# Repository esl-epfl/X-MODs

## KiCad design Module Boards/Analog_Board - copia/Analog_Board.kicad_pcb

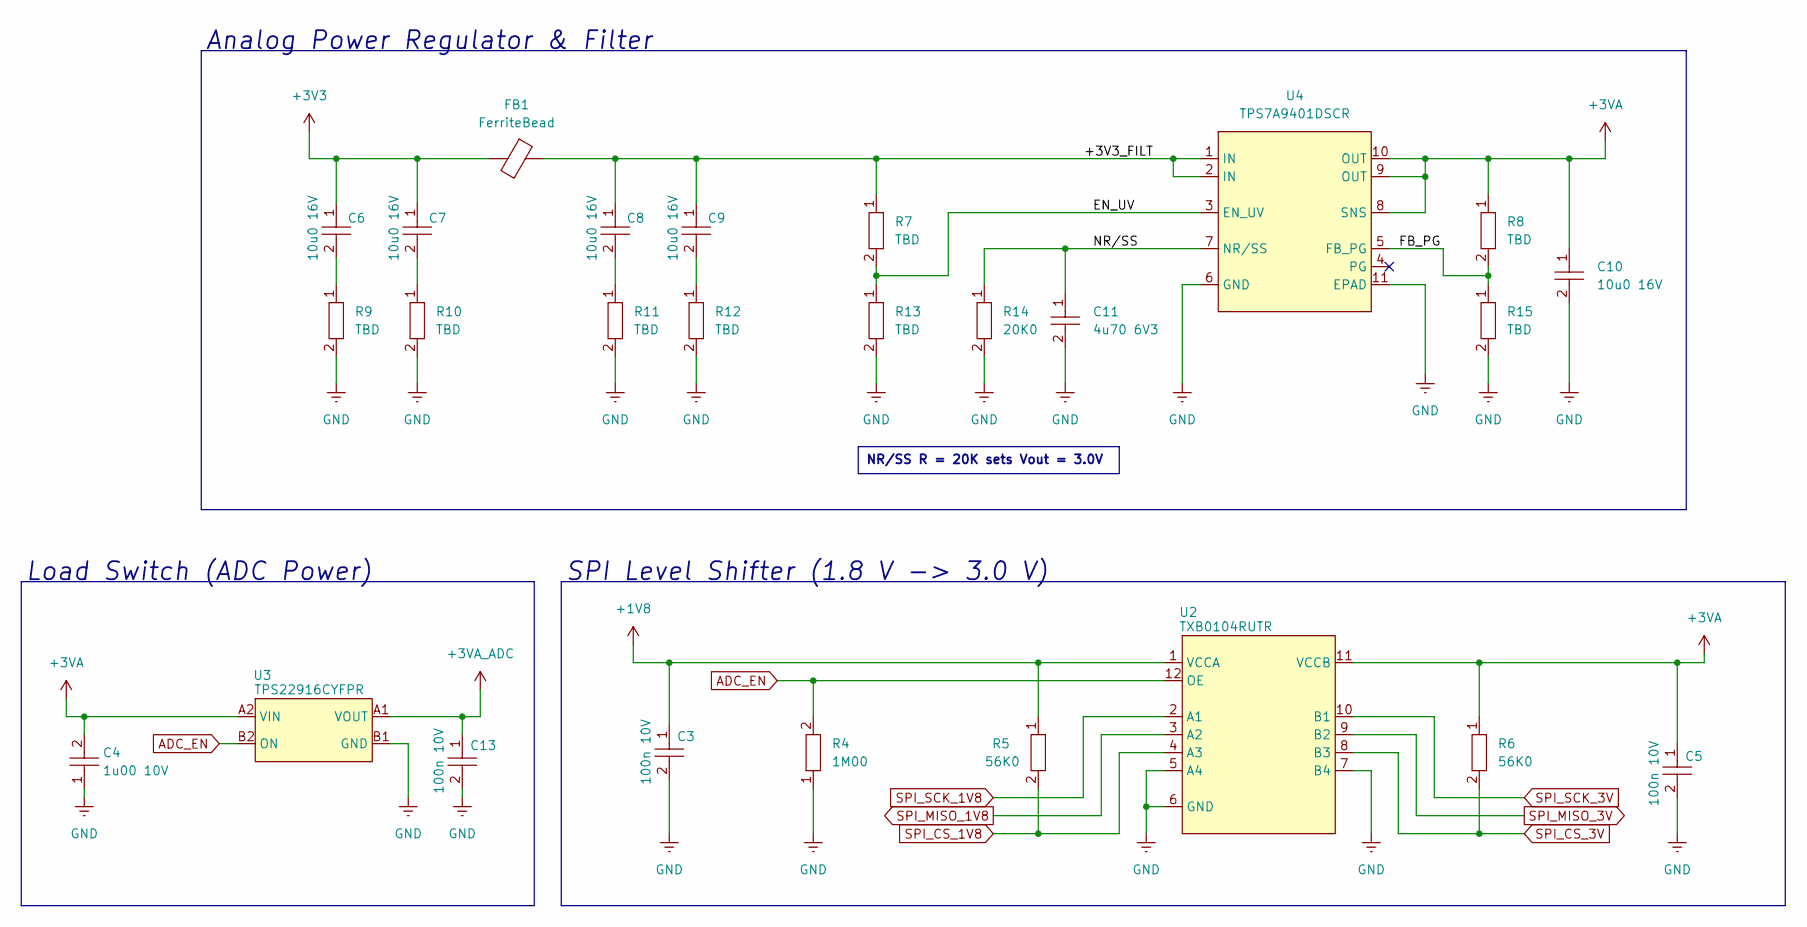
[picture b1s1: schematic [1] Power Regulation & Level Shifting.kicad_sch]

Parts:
C3, C5, C13: 100n 10V; C0402
C4: 1u00 10V; C0402
C6, C7, C8, C9, C10: 10u0 16V; C0402
C11: 4u70 6V3; C0402
FB1: FerriteBead; L0402
R4: 1M00; R0402
R5, R6: 56K0; R0402
R7, R8, R9, R10, R11, R12, R13, R15: TBD; R0402
R14: 20K0; R0402
U2: TXB0104RUTR; UQFN-12_1.7x2mm
U3: TPS22916CYFPR; DSBGA-4_0.74x0.74mm
U4: TPS7A9401DSCR; WSON-10-3.15x3.15mm

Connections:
+1V8: C3.1, R5.1, U2.1 (VCCA); also elsewhere on the board
+3V3: C6.1, C7.1, FB1.2; also elsewhere on the board
+3VA: C4.2, C5.1, C10.1, R6.1, R8.1, U2.11 (VCCB), U3.A2 (VIN), U4.8 (SNS), U4.9 (OUT), U4.10 (OUT)
+3VA_ADC: C13.1, U3.A1 (VOUT); also elsewhere on the board
/[1] Power Regulation & Level Shifting/+3V3_FILT: C8.1, C9.1, FB1.1, R7.1, U4.1 (IN), U4.2 (IN)
/[1] Power Regulation & Level Shifting/EN_UV: R7.2, R13.1, U4.3 (EN_UV)
/[1] Power Regulation & Level Shifting/FB_PG: R8.2, R15.1, U4.5 (FB_PG)
/[1] Power Regulation & Level Shifting/NR/SS: C11.1, R14.1, U4.7 (NR/SS)
ADC_EN: R4.2, U2.12 (OE), U3.B2 (ON); also elsewhere on the board
GND: C3.2, C4.1, C5.2, C10.2, C11.2, C13.2, R4.1, R9.2, R10.2, R11.2, R12.2, R13.2, R14.2, R15.2, U2.5 (A4), U2.6 (GND), U2.7 (B4), U3.B1 (GND), U4.6 (GND), U4.11 (EPAD); also elsewhere on the board
unnamed: C6.2, R9.1
unnamed: C7.2, R10.1
unnamed: C8.2, R11.1
unnamed: C9.2, R12.1
SPI_CS_1V8: R5.2, U2.4 (A3); also elsewhere on the board
SPI_CS_3V: R6.2, U2.8 (B3); also elsewhere on the board
SPI_MISO_1V8: U2.3 (A2); also elsewhere on the board
SPI_MISO_3V: U2.9 (B2); also elsewhere on the board
SPI_SCK_1V8: U2.2 (A1); also elsewhere on the board
SPI_SCK_3V: U2.10 (B1); also elsewhere on the board

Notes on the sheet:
NR/SS R = 20K sets Vout = 3.0V
Load Switch (ADC Power)
Analog Power Regulator & Filter
SPI Level Shifter (1.8 V -> 3.0 V)

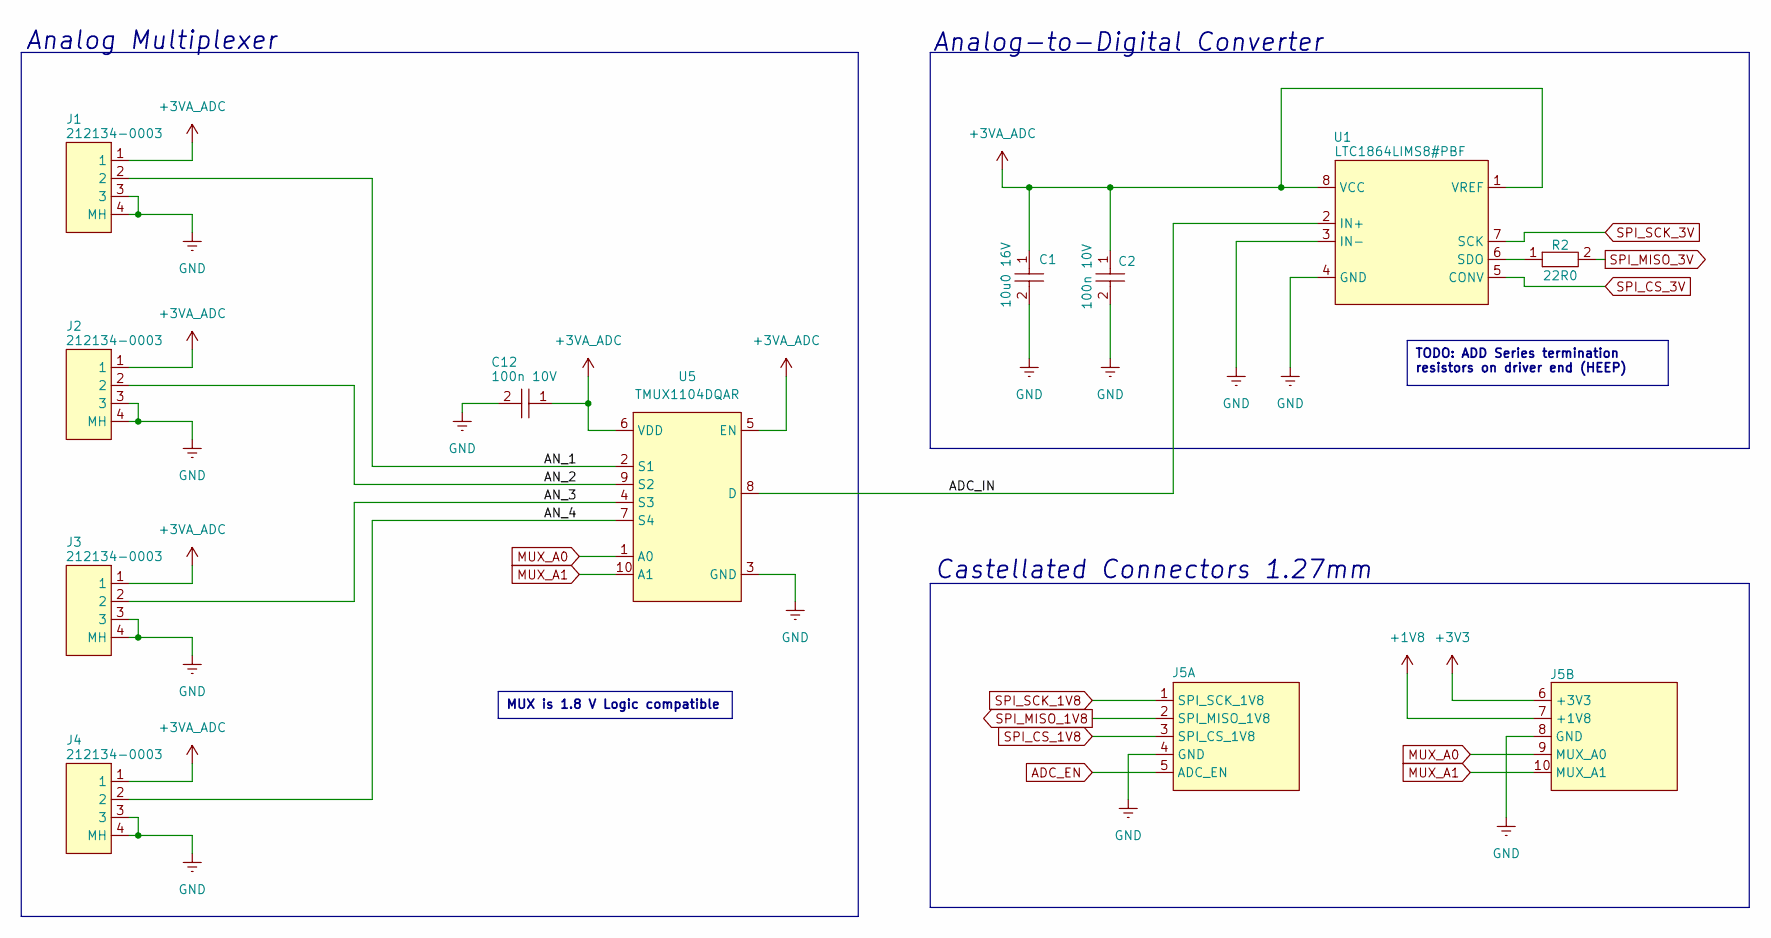
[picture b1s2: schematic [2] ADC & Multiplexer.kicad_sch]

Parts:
C1: 10u0 16V; C0402
C2, C12: 100n 10V; C0402
J1, J2, J3, J4: 212134-0003; 2121340003; MPN 212134-0003
J5: Analog_Board_Castellated_Conn_1.27mm
R2: 22R0; R0402
U1: LTC1864LIMS8#PBF; MSOP-8
U5: TMUX1104DQAR; USON-10_1x2.5mm; MPN TMUX1104DQAR

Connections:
+1V8: J5.7 (+1V8); also elsewhere on the board
+3V3: J5.6 (+3V3); also elsewhere on the board
+3VA_ADC: C1.1, C2.1, C12.1, J1.1, J2.1, J3.1, J4.1, U1.1 (VREF), U1.8 (VCC), U5.5 (EN), U5.6 (VDD); also elsewhere on the board
/[2] ADC & Multiplexer/ADC_IN: U1.2 (IN+), U5.8 (D)
/[2] ADC & Multiplexer/AN_1: J1.2, U5.2 (S1)
/[2] ADC & Multiplexer/AN_2: J2.2, U5.9 (S2)
/[2] ADC & Multiplexer/AN_3: J3.2, U5.4 (S3)
/[2] ADC & Multiplexer/AN_4: J4.2, U5.7 (S4)
ADC_EN: J5.5 (ADC_EN); also elsewhere on the board
GND: C1.2, C2.2, C12.2, J1.3, J1.4 (MH), J2.3, J2.4 (MH), J3.3, J3.4 (MH), J4.3, J4.4 (MH), J5.4 (GND), J5.8 (GND), U1.3 (IN-), U1.4 (GND), U5.3 (GND); also elsewhere on the board
MUX_A0: J5.9 (MUX_A0), U5.1 (A0)
MUX_A1: J5.10 (MUX_A1), U5.10 (A1)
unnamed: R2.1, U1.6 (SDO)
SPI_CS_1V8: J5.3 (SPI_CS_1V8); also elsewhere on the board
SPI_CS_3V: U1.5 (CONV); also elsewhere on the board
SPI_MISO_1V8: J5.2 (SPI_MISO_1V8); also elsewhere on the board
SPI_MISO_3V: R2.2; also elsewhere on the board
SPI_SCK_1V8: J5.1 (SPI_SCK_1V8); also elsewhere on the board
SPI_SCK_3V: U1.7 (SCK); also elsewhere on the board

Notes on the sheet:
MUX is 1.8 V Logic compatible
TODO: ADD Series termination resistors on driver end (HEEP)
Castellated Connectors 1.27mm
Analog-to-Digital Converter
Analog Multiplexer

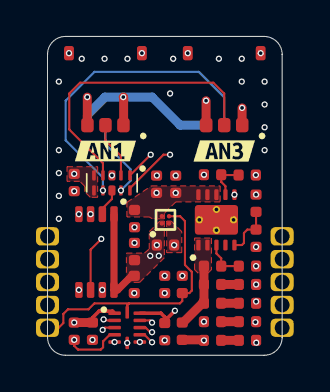
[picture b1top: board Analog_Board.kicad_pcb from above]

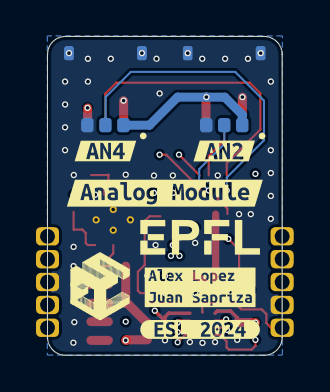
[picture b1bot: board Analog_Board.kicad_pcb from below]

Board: 6 copper layers, 13.0 x 17.7 mm, 44 parts (7 on the bottom side), 28 nets.

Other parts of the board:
kibuzzard-66E06AA7: G***; kibuzzard-66E06AA7
kibuzzard-67164A85: G***; kibuzzard-67164A85
kibuzzard-67164A89: G***; kibuzzard-67164A89
kibuzzard-671559FE: G***; kibuzzard-671559FE
kibuzzard-6716453A: G***; kibuzzard-6716453A
kibuzzard-67164525: G***; kibuzzard-67164525
kibuzzard-67165098: G***; kibuzzard-67165098

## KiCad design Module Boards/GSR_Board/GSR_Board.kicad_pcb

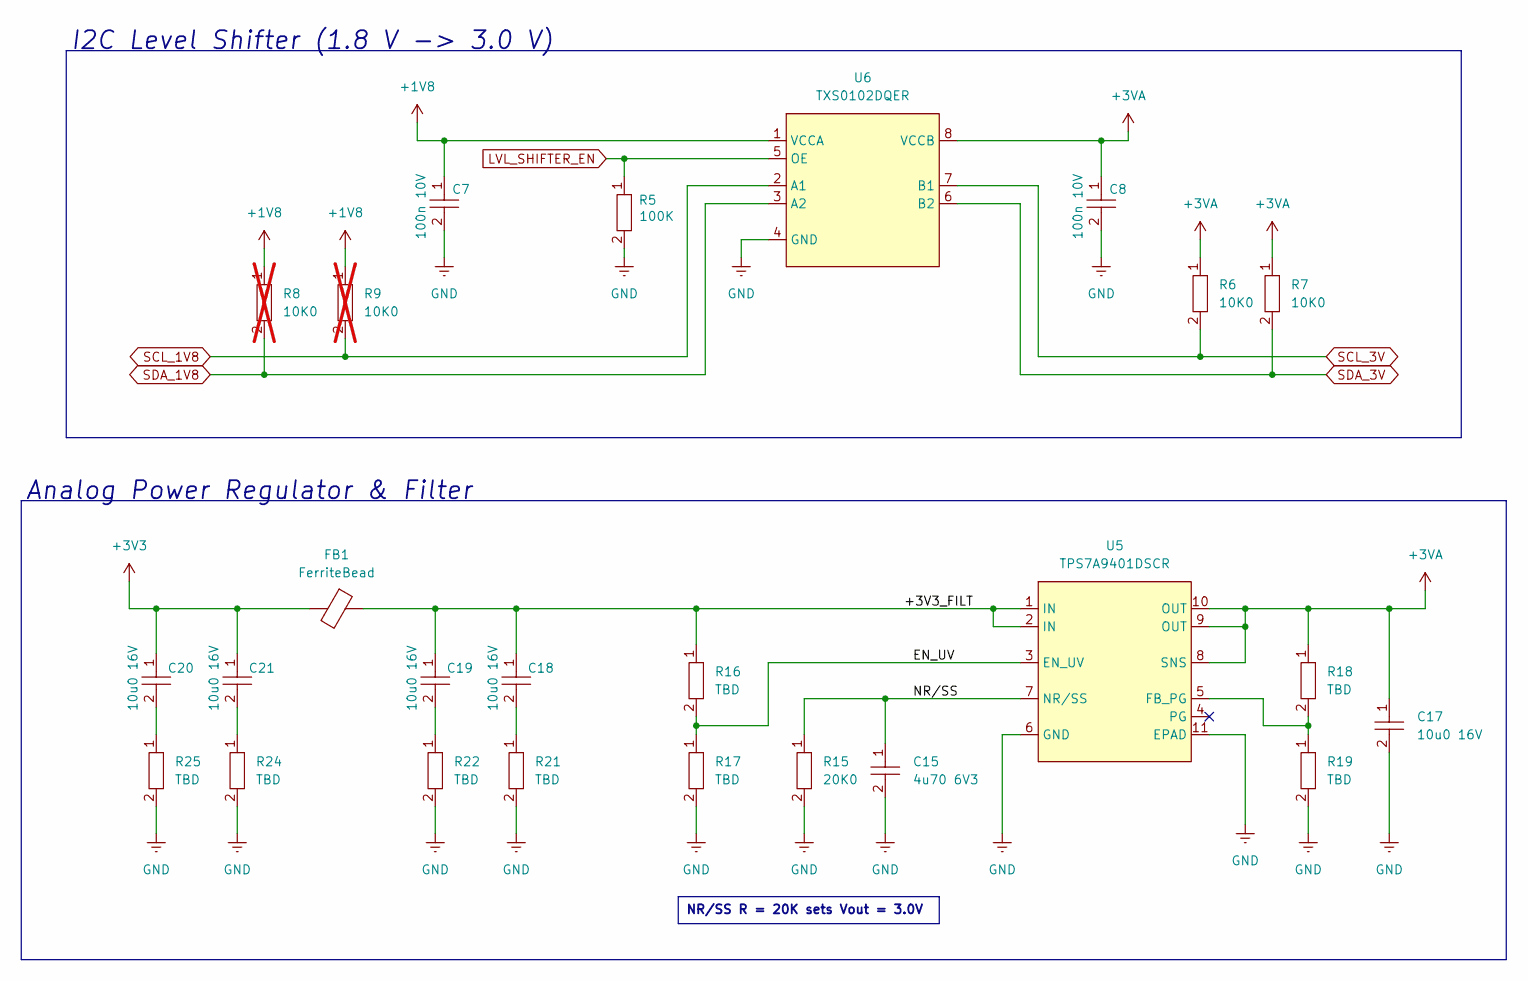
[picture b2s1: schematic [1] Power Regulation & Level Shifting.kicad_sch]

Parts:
C7, C8: 100n 10V; C0402
C15: 4u70 6V3; C0402
C17, C18, C19, C20, C21: 10u0 16V; C0402
FB1: FerriteBead; L0402
R5: 100K; R0402
R6, R7: 10K0; R0402
R8, R9: 10K0; R0402; not fitted
R15: 20K0; R0402
R16, R17, R18, R19, R21, R22, R24, R25: TBD; R0402
U5: TPS7A9401DSCR; WSON-10-3.15x3.15mm
U6: TXS0102DQER; X2SON-8

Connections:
+1V8: C7.1, R8.1, R9.1, U6.1 (VCCA); also elsewhere on the board
+3V3: C20.1, C21.1, FB1.2; also elsewhere on the board
+3VA: C8.1, C17.1, R6.1, R7.1, R18.1, U5.8 (SNS), U5.9 (OUT), U5.10 (OUT), U6.8 (VCCB); also elsewhere on the board
/[1] Power Regulation & Level Shifting/+3V3_FILT: C18.1, C19.1, FB1.1, R16.1, U5.1 (IN), U5.2 (IN)
/[1] Power Regulation & Level Shifting/EN_UV: R16.2, R17.1, U5.3 (EN_UV)
/[1] Power Regulation & Level Shifting/NR/SS: C15.1, R15.1, U5.7 (NR/SS)
GND: C7.2, C8.2, C15.2, C17.2, R5.2, R15.2, R17.2, R19.2, R21.2, R22.2, R24.2, R25.2, U5.6 (GND), U5.11 (EPAD), U6.4 (GND); also elsewhere on the board
LVL_SHIFTER_EN: R5.1, U6.5 (OE); also elsewhere on the board
unnamed: C18.2, R21.1
unnamed: C19.2, R22.1
unnamed: C20.2, R25.1
unnamed: C21.2, R24.1
unnamed: R18.2, R19.1, U5.5 (FB_PG)
SCL_1V8: R9.2, U6.2 (A1); also elsewhere on the board
SCL_3V: R6.2, U6.7 (B1); also elsewhere on the board
SDA_1V8: R8.2, U6.3 (A2); also elsewhere on the board
SDA_3V: R7.2, U6.6 (B2); also elsewhere on the board

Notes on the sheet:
NR/SS R = 20K sets Vout = 3.0V
I2C Level Shifter (1.8 V -> 3.0 V)
Analog Power Regulator & Filter

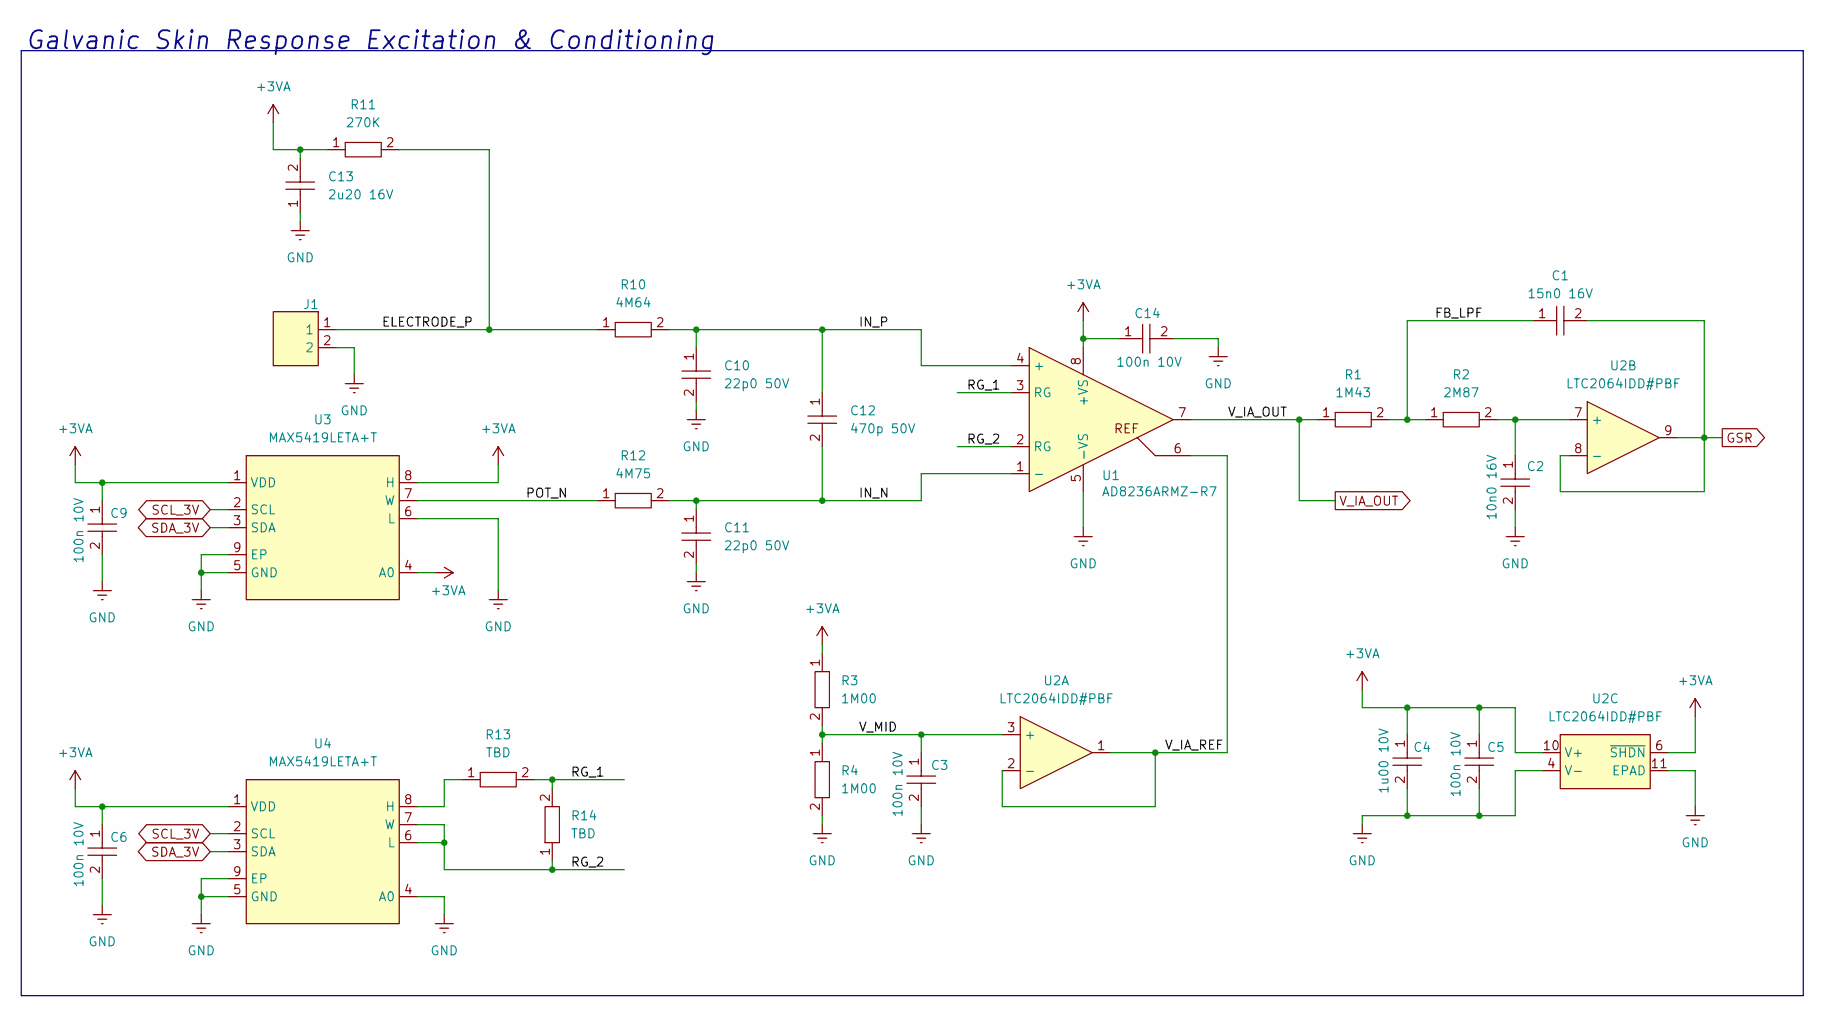
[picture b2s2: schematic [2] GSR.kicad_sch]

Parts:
C1: 15n0 16V; C0402
C2: 10n0 16V; C0402
C3, C5, C6, C9, C14: 100n 10V; C0402
C4: 1u00 10V; C0402
C10, C11: 22p0 50V; C0402
C12: 470p 50V; C0402
C13: 2u20 16V; C0402
J1: GSR_Electrodes_Conn
R1: 1M43; R0402
R2: 2M87; R0402
R3, R4: 1M00; R0402
R10: 4M64; R0402
R11: 270K; R0402
R12: 4M75; R0402
R13, R14: TBD; R0402
U1: AD8236ARMZ-R7; MSOP-8
U2: LTC2064IDD#PBF; DFN-10_3x3mm
U3, U4: MAX5419LETA+T; TDFN-8_3x3mm

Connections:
+3VA: C4.1, C5.1, C6.1, C9.1, C13.2, C14.1, R3.1, R11.1, U1.8 (+VS), U2.6 (~SHDN), U2.10 (V+), U3.1 (VDD), U3.4 (A0), U3.8 (H), U4.1 (VDD); also elsewhere on the board
/[2] GSR/ELECTRODE_P: J1.1, R10.1, R11.2
/[2] GSR/FB_LPF: C1.1, R1.2, R2.1
/[2] GSR/IN_N: C11.1, C12.2, R12.2, U1.1 (-)
/[2] GSR/IN_P: C10.1, C12.1, R10.2, U1.4 (+)
/[2] GSR/POT_N: R12.1, U3.7 (W)
/[2] GSR/RG_1: R13.2, R14.2, U1.3 (RG)
/[2] GSR/RG_2: R14.1, U1.2 (RG), U4.6 (L), U4.7 (W)
/[2] GSR/V_IA_REF: U1.6, U2.1, U2.2 (-)
/[2] GSR/V_MID: C3.1, R3.2, R4.1, U2.3 (+)
GND: C2.2, C3.2, C4.2, C5.2, C6.2, C9.2, C10.2, C11.2, C13.1, C14.2, J1.2, R4.2, U1.5 (-VS), U2.4 (V-), U2.11 (EPAD), U3.5 (GND), U3.6 (L), U3.9 (EP), U4.4 (A0), U4.5 (GND), U4.9 (EP); also elsewhere on the board
GSR: C1.2, U2.8 (-), U2.9; also elsewhere on the board
unnamed: C2.1, R2.2, U2.7 (+)
unnamed: R13.1, U4.8 (H)
SCL_3V: U3.2 (SCL), U4.2 (SCL); also elsewhere on the board
SDA_3V: U3.3 (SDA), U4.3 (SDA); also elsewhere on the board
V_IA_OUT: R1.1, U1.7; also elsewhere on the board

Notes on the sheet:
Galvanic Skin Response Excitation & Conditioning

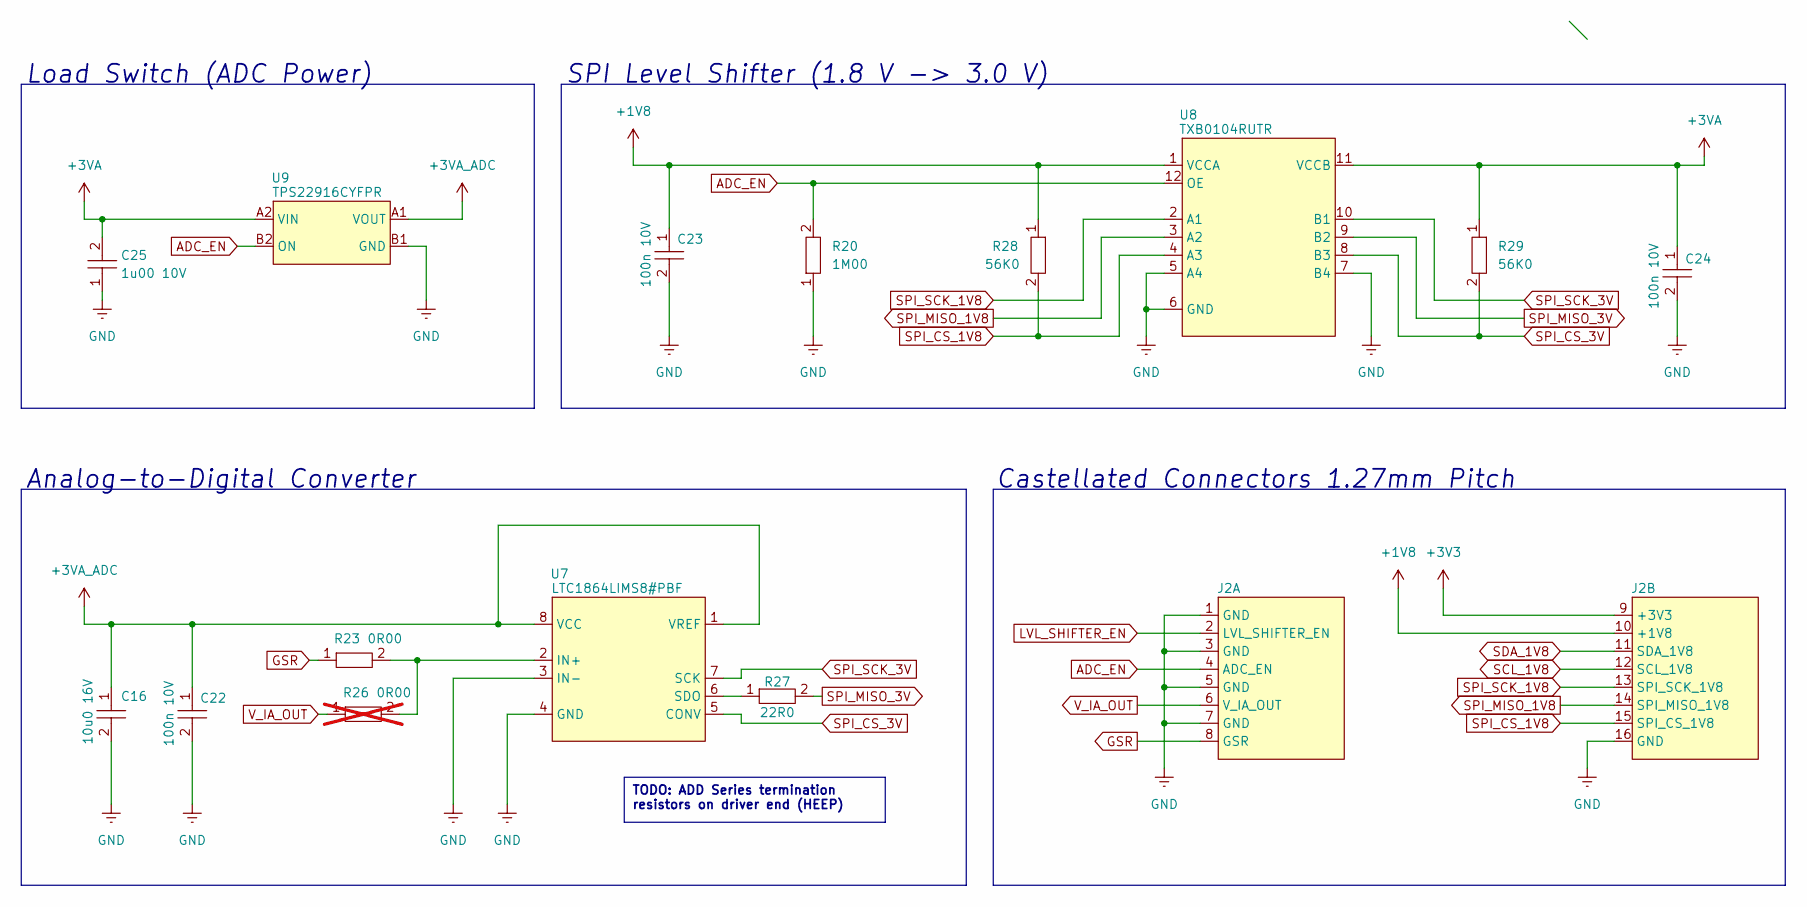
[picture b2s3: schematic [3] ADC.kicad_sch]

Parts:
C16: 10u0 16V; C0402
C22, C23, C24: 100n 10V; C0402
C25: 1u00 10V; C0402
J2: GSR_Board_Castellated_Conn_1.27mm
R20: 1M00; R0402
R23: 0R00; R0402
R26: 0R00; R0402; not fitted
R27: 22R0; R0402
R28, R29: 56K0; R0402
U7: LTC1864LIMS8#PBF; MSOP-8
U8: TXB0104RUTR; UQFN-12_1.7x2mm
U9: TPS22916CYFPR; DSBGA-4_0.74x0.74mm

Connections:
+1V8: C23.1, J2.10 (+1V8), R28.1, U8.1 (VCCA); also elsewhere on the board
+3V3: J2.9 (+3V3); also elsewhere on the board
+3VA: C24.1, C25.2, R29.1, U8.11 (VCCB), U9.A2 (VIN); also elsewhere on the board
+3VA_ADC: C16.1, C22.1, U7.1 (VREF), U7.8 (VCC), U9.A1 (VOUT)
ADC_EN: J2.4 (ADC_EN), R20.2, U8.12 (OE), U9.B2 (ON)
GND: C16.2, C22.2, C23.2, C24.2, C25.1, J2.1 (GND), J2.3 (GND), J2.5 (GND), J2.7 (GND), J2.16 (GND), R20.1, U7.3 (IN-), U7.4 (GND), U8.5 (A4), U8.6 (GND), U8.7 (B4), U9.B1 (GND); also elsewhere on the board
GSR: J2.8 (GSR), R23.1; also elsewhere on the board
LVL_SHIFTER_EN: J2.2 (LVL_SHIFTER_EN); also elsewhere on the board
unnamed: R23.2, R26.2, U7.2 (IN+)
unnamed: R27.1, U7.6 (SDO)
SCL_1V8: J2.12 (SCL_1V8); also elsewhere on the board
SDA_1V8: J2.11 (SDA_1V8); also elsewhere on the board
SPI_CS_1V8: J2.15 (SPI_CS_1V8), R28.2, U8.4 (A3)
SPI_CS_3V: R29.2, U7.5 (CONV), U8.8 (B3)
SPI_MISO_1V8: J2.14 (SPI_MISO_1V8), U8.3 (A2)
SPI_MISO_3V: R27.2, U8.9 (B2)
SPI_SCK_1V8: J2.13 (SPI_SCK_1V8), U8.2 (A1)
SPI_SCK_3V: U7.7 (SCK), U8.10 (B1)
V_IA_OUT: J2.6 (V_IA_OUT), R26.1; also elsewhere on the board

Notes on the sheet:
TODO: ADD Series termination resistors on driver end (HEEP)
Load Switch (ADC Power)
SPI Level Shifter (1.8 V -> 3.0 V)
Analog-to-Digital Converter
Castellated Connectors 1.27mm Pitch

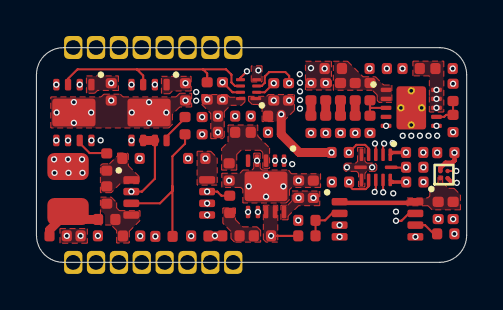
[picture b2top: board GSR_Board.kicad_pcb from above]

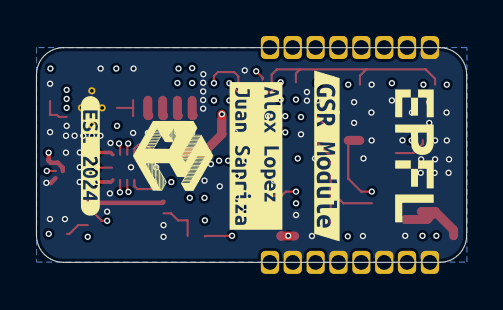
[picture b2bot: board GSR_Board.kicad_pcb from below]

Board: 6 copper layers, 23.9 x 11.9 mm, 69 parts (3 on the bottom side), 40 nets.

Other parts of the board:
kibuzzard-66E06AA7: G***; kibuzzard-66E06AA7
kibuzzard-66E06AC0: G***; kibuzzard-66E06AC0
kibuzzard-66FA4FC2: G***; kibuzzard-66FA4FC2

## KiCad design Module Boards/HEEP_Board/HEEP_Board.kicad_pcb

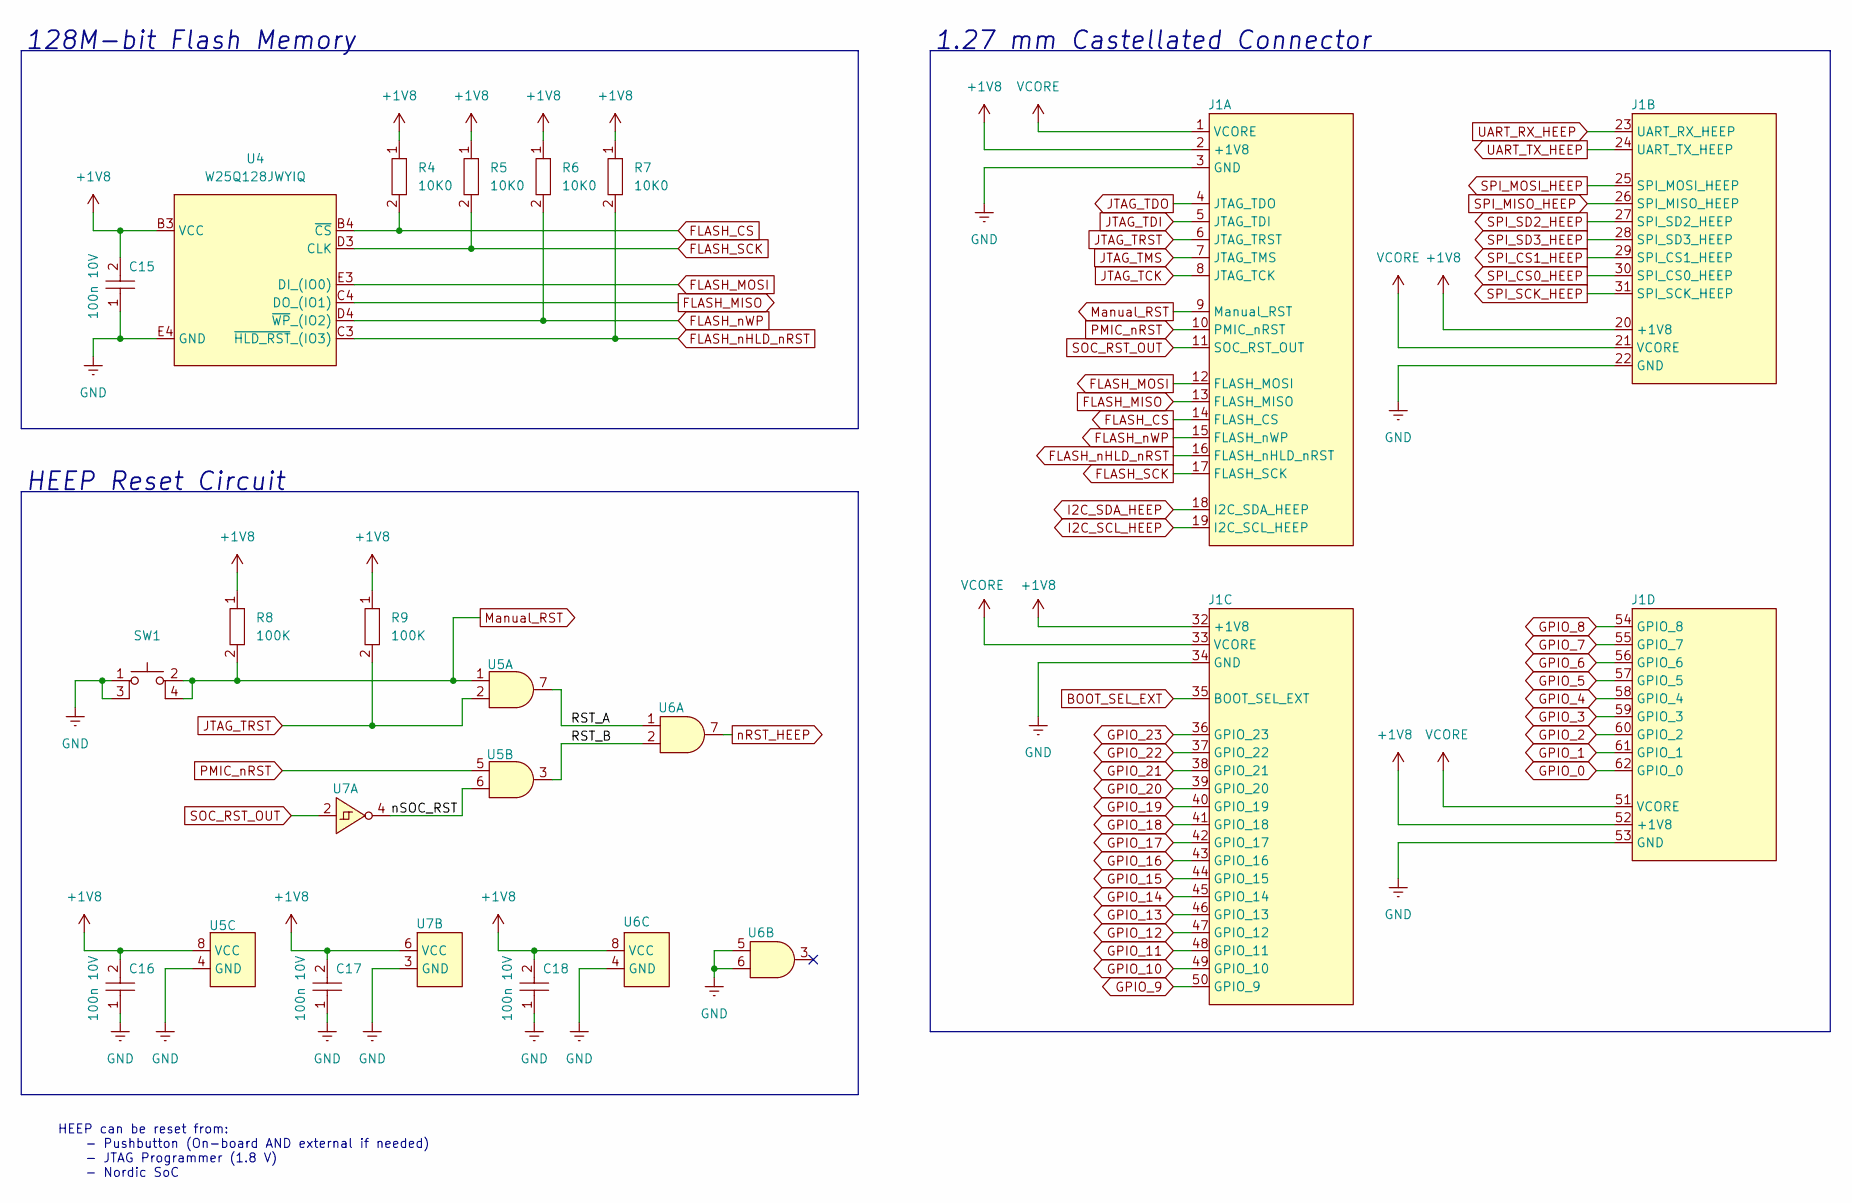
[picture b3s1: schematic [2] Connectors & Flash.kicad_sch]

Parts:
C15, C16, C17, C18: 100n 10V; C0402
J1: HEEP_Board_Castellated_Conn_1.27mm
R4, R5, R6, R7: 10K0; R0402
R8, R9: 100K; R0402
SW1: TL1030AF160AQJ
U4: W25Q128JWYIQ; WLCSP-21
U5, U6: X2SON-8
U7: X2SON-6

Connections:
+1V8: C15.2, C16.2, C17.2, C18.2, J1.2 (+1V8), J1.20 (+1V8), J1.32 (+1V8), J1.52 (+1V8), R4.1, R5.1, R6.1, R7.1, R8.1, R9.1, U4.B3 (VCC), U5.8 (VCC), U6.8 (VCC), U7.6 (VCC); also elsewhere on the board
/[2] Connectors & Flash/RST_A: U5.7, U6.1
/[2] Connectors & Flash/RST_B: U5.3, U6.2
/[2] Connectors & Flash/nSOC_RST: U5.6, U7.4
BOOT_SEL_EXT: J1.35 (BOOT_SEL_EXT); also elsewhere on the board
FLASH_CS: J1.14 (FLASH_CS), R4.2, U4.B4 (~CS); also elsewhere on the board
FLASH_MISO: J1.13 (FLASH_MISO), U4.C4 (DO_(IO1)); also elsewhere on the board
FLASH_MOSI: J1.12 (FLASH_MOSI), U4.E3 (DI_(IO0)); also elsewhere on the board
FLASH_SCK: J1.17 (FLASH_SCK), R5.2, U4.D3 (CLK); also elsewhere on the board
FLASH_nHLD_nRST: J1.16 (FLASH_nHLD_nRST), R7.2, U4.C3 (~HLD_RST_(IO3)); also elsewhere on the board
FLASH_nWP: J1.15 (FLASH_nWP), R6.2, U4.D4 (~WP_(IO2)); also elsewhere on the board
GND: C15.1, C16.1, C17.1, C18.1, J1.3 (GND), J1.22 (GND), J1.34 (GND), J1.53 (GND), SW1.1, SW1.3, U4.E4 (GND), U5.4 (GND), U6.4 (GND), U6.5, U6.6, U7.3 (GND); also elsewhere on the board
GPIO_0: J1.62 (GPIO_0); also elsewhere on the board
GPIO_1: J1.61 (GPIO_1); also elsewhere on the board
GPIO_2: J1.60 (GPIO_2); also elsewhere on the board
GPIO_3: J1.59 (GPIO_3); also elsewhere on the board
GPIO_4: J1.58 (GPIO_4); also elsewhere on the board
GPIO_5: J1.57 (GPIO_5); also elsewhere on the board
GPIO_6: J1.56 (GPIO_6); also elsewhere on the board
GPIO_7: J1.55 (GPIO_7); also elsewhere on the board
GPIO_8: J1.54 (GPIO_8); also elsewhere on the board
GPIO_9: J1.50 (GPIO_9); also elsewhere on the board
GPIO_10: J1.49 (GPIO_10); also elsewhere on the board
GPIO_11: J1.48 (GPIO_11); also elsewhere on the board
GPIO_12: J1.47 (GPIO_12); also elsewhere on the board
GPIO_13: J1.46 (GPIO_13); also elsewhere on the board
GPIO_14: J1.45 (GPIO_14); also elsewhere on the board
GPIO_15: J1.44 (GPIO_15); also elsewhere on the board
GPIO_16: J1.43 (GPIO_16); also elsewhere on the board
GPIO_17: J1.42 (GPIO_17); also elsewhere on the board
GPIO_18: J1.41 (GPIO_18); also elsewhere on the board
GPIO_19: J1.40 (GPIO_19); also elsewhere on the board
GPIO_20: J1.39 (GPIO_20); also elsewhere on the board
GPIO_21: J1.38 (GPIO_21); also elsewhere on the board
GPIO_22: J1.37 (GPIO_22); also elsewhere on the board
GPIO_23: J1.36 (GPIO_23); also elsewhere on the board
I2C_SCL_HEEP: J1.19 (I2C_SCL_HEEP); also elsewhere on the board
I2C_SDA_HEEP: J1.18 (I2C_SDA_HEEP); also elsewhere on the board
JTAG_TCK: J1.8 (JTAG_TCK); also elsewhere on the board
JTAG_TDI: J1.5 (JTAG_TDI); also elsewhere on the board
JTAG_TDO: J1.4 (JTAG_TDO); also elsewhere on the board
JTAG_TMS: J1.7 (JTAG_TMS); also elsewhere on the board
JTAG_TRST: J1.6 (JTAG_TRST), R9.2, U5.2; also elsewhere on the board
Manual_RST: J1.9 (Manual_RST), R8.2, SW1.2, SW1.4, U5.1
PMIC_nRST: J1.10 (PMIC_nRST), U5.5
SOC_RST_OUT: J1.11 (SOC_RST_OUT), U7.2
SPI_CS0_HEEP: J1.30 (SPI_CS0_HEEP); also elsewhere on the board
SPI_CS1_HEEP: J1.29 (SPI_CS1_HEEP); also elsewhere on the board
SPI_MISO_HEEP: J1.26 (SPI_MISO_HEEP); also elsewhere on the board
SPI_MOSI_HEEP: J1.25 (SPI_MOSI_HEEP); also elsewhere on the board
SPI_SCK_HEEP: J1.31 (SPI_SCK_HEEP); also elsewhere on the board
SPI_SD2_HEEP: J1.27 (SPI_SD2_HEEP); also elsewhere on the board
SPI_SD3_HEEP: J1.28 (SPI_SD3_HEEP); also elsewhere on the board
UART_RX_HEEP: J1.23 (UART_RX_HEEP); also elsewhere on the board
UART_TX_HEEP: J1.24 (UART_TX_HEEP); also elsewhere on the board
VCORE: J1.1 (VCORE), J1.21 (VCORE), J1.33 (VCORE), J1.51 (VCORE); also elsewhere on the board
nRST_HEEP: U6.7; also elsewhere on the board

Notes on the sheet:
HEEP Reset Circuit
HEEP can be reset from: - Pushbutton (On-board AND external if needed) - JTAG Programmer (1.8 V) - Nordic SoC
1.27 mm Castellated Connector
128M-bit Flash Memory
